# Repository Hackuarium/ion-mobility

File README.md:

# What is Ion Mobility Spectrometry ?

[https://en.wikipedia.org/wiki/Ion-mobility_spectrometry]

# Why should we do this ?

There are numerous application for IMS and it has the main advantage to work at atmospheric pressure (in constraste with mass spectrometry that requires most of the time 10-3 torr) that would make it compact and affordable.

We see the possibility to make continious monitoring of the bioreactor made by Hackuarium and situated in Cali, Colombia.

# Can we do a Ion Mobility Spectrometer our self ?

Main parts of the IMS :

- Desolvation zone : Insert and ionization of sample. 
Electrospray ionisation (ESI). Advantage : one can insert the liquid sample and ionize it through the same needle. 
Limitation : 5kV voltage source, 100uL/min flow rate through the needle. 

- Shutter : Let the ions pass on command.
Three grid Shutter. Advantage : easy to built and to command. 

- Drift zone : Acceleration of ions.
Made by multiple electrodes connected to different voltages with the aid of a voltage divider. 
Limitation : 10kV voltage source. 

- Detection : Faraday plate.
Transconductance amplifier converts the tiny ion current into a reasonable tension.
Limitation : The current-to-tension AOP must be with very low bias current, and low noise (hence expensive). 

- Monitoring : A/D converter. 

Link to full project already made : [https://github.com/bhclowers/OS-IMS]

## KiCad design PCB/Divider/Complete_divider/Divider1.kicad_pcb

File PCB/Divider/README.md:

# Divider

## Description

Printed circuit board of the two voltage dividers for the desolvation region and the drift tube/region. Connects all electrodes together with 10 M $\Omega$ in between each of them, to create a continuous voltage gradient and thus an electric field to accelerate the ions. 

## Specifications and limitations

The highest voltage is 11.5 kV at the first electrode, down to the ground connected last electrode, and the target at the end of the drift tube.

Higher resistors in between the electrodes doesn't change the voltage gradient but reduces the current and thus the electrical consumption.

## PCB

Below are pictures of the PCBs. First one is desolvation region and second one is drift region.

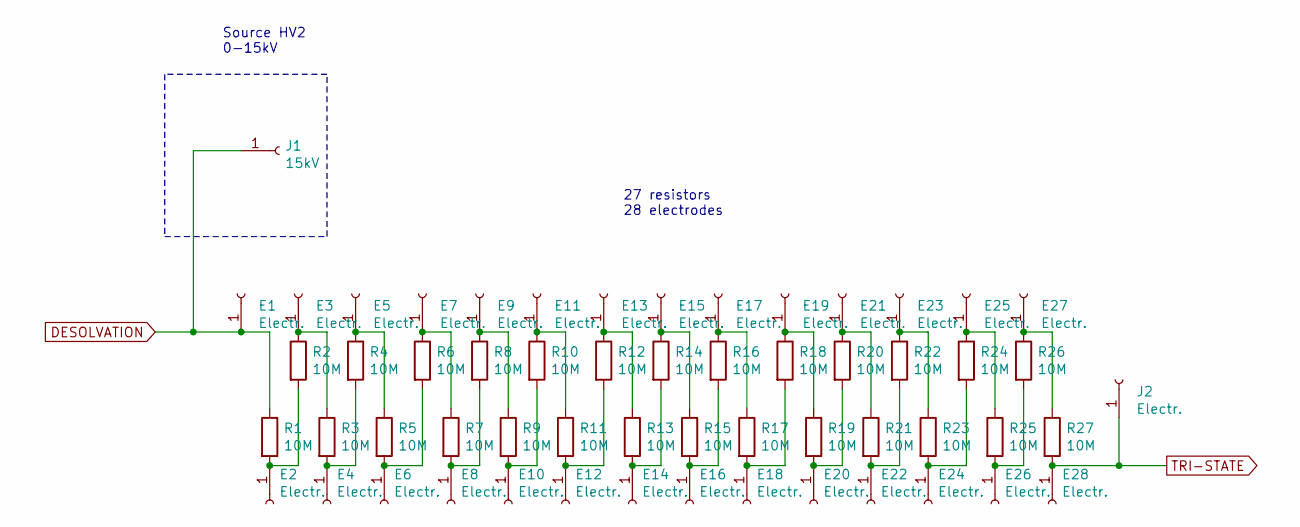
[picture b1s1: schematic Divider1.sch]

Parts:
E1, E2, E3, E4, E5, E6, E7, E8, E9, E10, E11, E12, E13, E14, E15, E16, E17, E18, E19, E20, E21, E22, E23, E24, E25, E26, E27, E28: Electr.; Pad_for_electrode
J1: 15kV; Pin_D1.4mm_L8.5mm_W2.8mm_FlatFork
J2: Electr.; Pin_D1.0mm_L10.0mm
R1, R2, R3, R4, R5, R6, R7, R8, R9, R10, R11, R12, R13, R14, R15, R16, R17, R18, R19, R20, R21, R22, R23, R24, R25, R26, R27: 10M; R_1206_3216Metric_Pad1.42x1.75mm_HandSolder

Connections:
DESOLVATION: E1.1, J1.1, R1.1
unnamed: E2.1, R1.2, R2.2
unnamed: E3.1, R2.1, R3.1
unnamed: E4.1, R3.2, R4.2
unnamed: E5.1, R4.1, R5.1
unnamed: E6.1, R5.2, R6.2
unnamed: E7.1, R6.1, R7.1
unnamed: E8.1, R7.2, R8.2
unnamed: E9.1, R8.1, R9.1
unnamed: E10.1, R9.2, R10.2
unnamed: E11.1, R10.1, R11.1
unnamed: E12.1, R11.2, R12.2
unnamed: E13.1, R12.1, R13.1
unnamed: E14.1, R13.2, R14.2
unnamed: E15.1, R14.1, R15.1
unnamed: E16.1, R15.2, R16.2
unnamed: E17.1, R16.1, R17.1
unnamed: E18.1, R17.2, R18.2
unnamed: E19.1, R18.1, R19.1
unnamed: E20.1, R19.2, R20.2
unnamed: E21.1, R20.1, R21.1
unnamed: E22.1, R21.2, R22.2
unnamed: E23.1, R22.1, R23.1
unnamed: E24.1, R23.2, R24.2
unnamed: E25.1, R24.1, R25.1
unnamed: E26.1, R25.2, R26.2
unnamed: E27.1, R26.1, R27.1
TRI-STATE: E28.1, J2.1, R27.2

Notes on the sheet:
Source HV2 0-15kV
27 resistors 28 electrodes

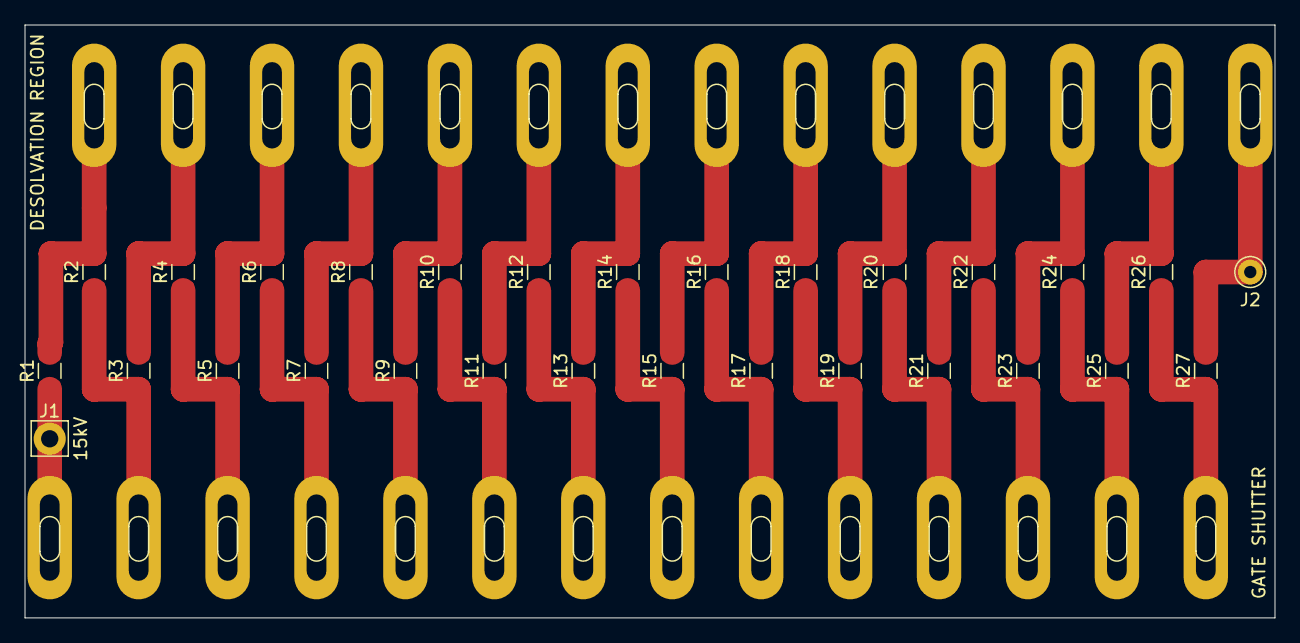
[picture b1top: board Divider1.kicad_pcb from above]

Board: 2 copper layers, 101.2 x 48.0 mm, 57 parts (0 on the bottom side), 28 nets.

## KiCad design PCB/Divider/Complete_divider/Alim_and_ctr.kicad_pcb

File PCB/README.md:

In order to better understand the overall electrical diagram and the paper’s resistance choice, an equivalent electrical diagram of the IMS from the first electrode to the amplifier is shown below. 

Thanks to those equations, we see that when the gate is closed, the potential of the second grid is higher than when it is opened. In the paper, they recommend adding 30 to 80 V (referenced to ”small” in the equations) to stop the flow of electrons. According to the calculations, a value of 50V or higher would result in a reverse electric field and effectively close the gate. 

These calculations are based on the paper’s values, not those of the current prototype. For the moment, the resistors on the divider PCB are 10 MΩ, designed to reduce power consumption. But this does not seem necessary, since with 1 MΩ resistors, power consumption is already only 160 to 200 μA, and changing the resistor of the dividers would also mean adapting the other resistors of the circuit.

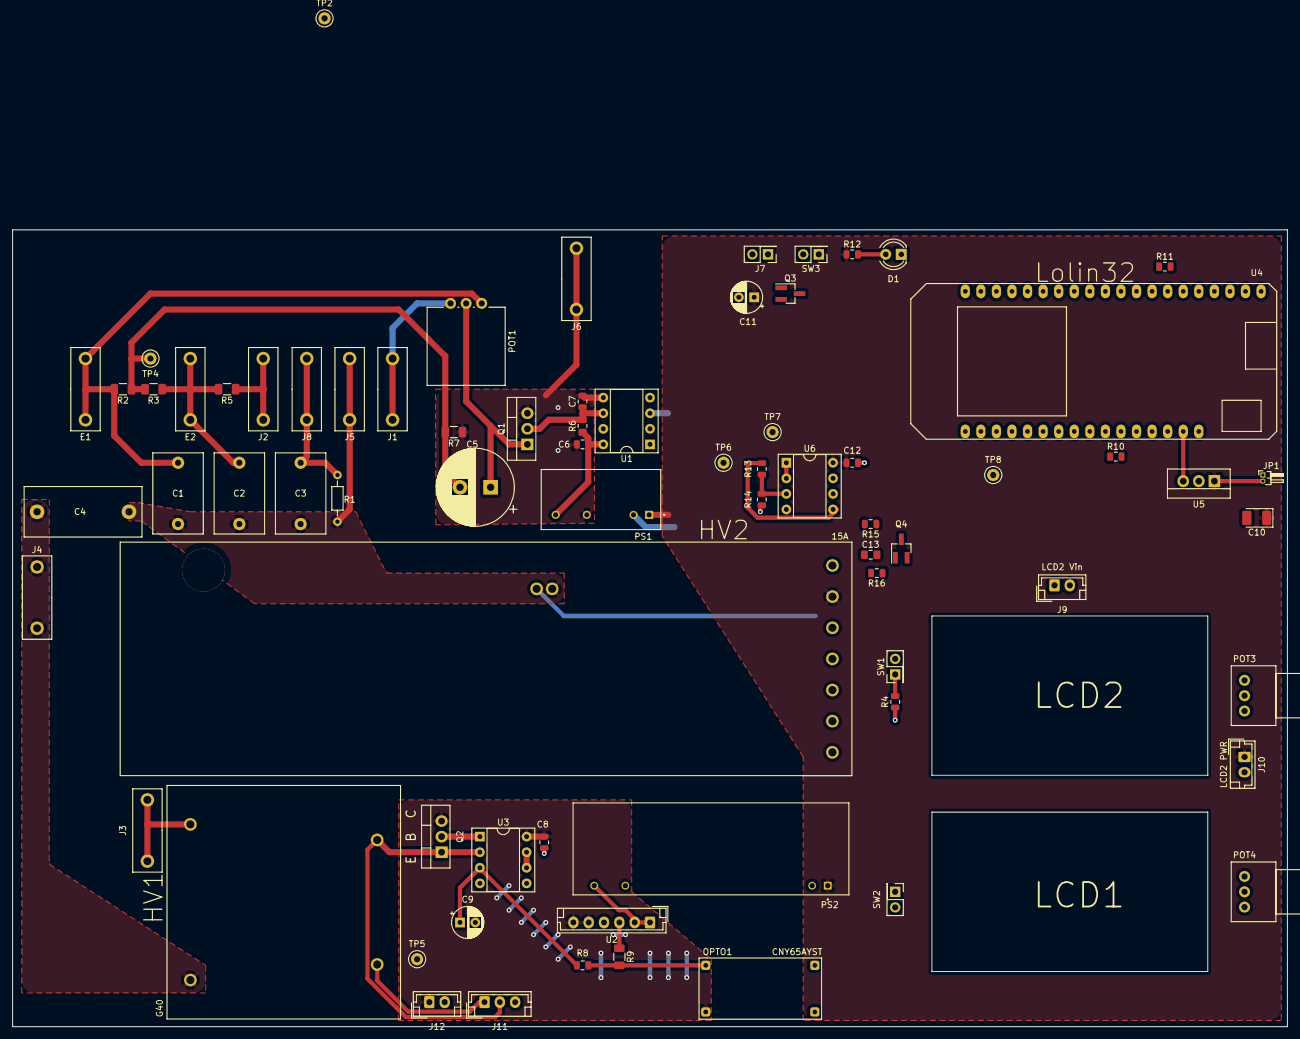
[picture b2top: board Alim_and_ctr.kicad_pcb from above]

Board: 2 copper layers, 208.0 x 130.0 mm, 72 parts (0 on the bottom side), 47 nets.

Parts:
C1, C2: 4700pF 10kV; C_Rect_L13.0mm_W8.0mm_P10.00mm_FKS3_FKP3_MKS4
C3: 0.22uF; C_Rect_L13.0mm_W8.0mm_P10.00mm_FKS3_FKP3_MKS4
C4: 2500pF 15 kV; C_Rect_L19.0mm_W8.0mm_P15.00mm_MKS4
C5: 47uF/100V; CP_Radial_D12.5mm_P5.00mm
C6, C8, C12: 100nF; C_0805_2012Metric
C7: 15pF; C_0805_2012Metric
C9: 2,2uF; CP_Radial_D5.0mm_P2.50mm
C10: 0.33uF Tant.; CP_EIA-3528-21_Kemet-B_Pad1.50x2.35mm_HandSolder
C11: 100uF; CP_Radial_D5.0mm_P2.50mm
C13: 2,2uF; C_0805_2012Metric_Pad1.15x1.40mm_HandSolder
D1: PWR LED; LED_D4.0mm
E1: Mid electrode1; conn_HV_JACK_PB1021
E2: Mid electrode2; conn_HV_JACK_PB1021
HV1: G40
HV2: 15A
J1: Electrode in; conn_HV_JACK_PB1021
J2: Electrode out; conn_HV_JACK_PB1021
J3, J4: HV out; conn_HV_JACK_PB1021
J5: Last Electrode; conn_HV_JACK_PB1021
J6: Gate; conn_HV_JACK_PB1021
J7: 12V in; PinHeader_2x01_P2.54mm_Vertical
J8: Ap Grid; conn_HV_JACK_PB1021
J9: LCD2 Vin; JST_EH_B2B-EH-A_1x02_P2.50mm_Vertical
J10: LCD2 PWR; JST_EH_B2B-EH-A_1x02_P2.50mm_Vertical
J11: LCD1 V/I measures; JST_EH_B3B-EH-A_1x03_P2.50mm_Vertical
J12: LCD1 PWR; JST_EH_B2B-EH-A_1x02_P2.50mm_Vertical
JP1: Jumper; PinHeader_1x02_P1.00mm_Horizontal
OPTO1: CNY65AYST
POT1: 10M; Potentiometer_Vishay_148-149_Single_Vertical
POT3, POT4: 50K; Potentiometer_Alps_RK097_Single_Horizontal
PS1: RHV2-1212S/R20; R8
PS2: RHV2-1212S/R20; R20
Q1: ZVN2110A; TO-220-3_Vertical
Q2: ZTX1053A; TO-220-3_Vertical
Q3: SSM3J340R; SOT-23_Handsoldering
Q4: ZTX1053A; SOT-23_Handsoldering
R1: 500K; R_Axial_DIN0204_L3.6mm_D1.6mm_P7.62mm_Horizontal
R2, R3: 1.5M; R_1206_3216Metric
R4, R14: 1M; R_0805_2012Metric
R5: 10M; R_1206_3216Metric
R6: 5K; R_0805_2012Metric_Pad1.15x1.40mm_HandSolder
R7: 50R; R_1206_3216Metric
R8, R15, R16: 20K; R_0805_2012Metric
R9: 1K; R_1206_3216Metric
R10, R11: 100R; R_0805_2012Metric
R12: R_LED; R_0805_2012Metric
R13: 3.3M; R_0805_2012Metric
SW1: EN switch; PinHeader_2x01_P2.54mm_Vertical
SW2: HV1 Switch; PinHeader_2x01_P2.54mm_Vertical
SW3: PWR switch; PinHeader_2x01_P2.54mm_Vertical
TP2, TP4, TP5, TP6, TP7, TP8: TestPoint; TestPoint_Keystone_5000-5004_Miniature
U1: 6N137A; DIP-8_W7.62mm_Socket
U2: mEZD41501A-X; JST_EH_B6B-EH-A_1x06_P2.50mm_Vertical
U3: LM358; DIP-8_W7.62mm_Socket
U4: Lolin32
U5: MC78M15ACTG; TO-262-3_Vertical
U6: LM358P; DIP-8_W7.62mm_Socket

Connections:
+3V3: POT3.1, POT4.1, U4.1, U4.20
+5V: JP1.1, Q4.3, U5.3
+12V: C10.1, C11.1, C12.2, HV2.2, J10.1, PS1.1, PS2.1, R12.1, SW3.1, U5.1, U6.8
+12VA: C6.1, PS1.4, R6.1, U1.8
+15V: C8.1, J12.1, OPTO1.4, Q2.3, U2.5, U2.6, U3.8
/Aperture_Grid: C3.1, J8.1, R1.1
/Middle_electrode1: C1.1, E1.1, POT1.3, R2.2
/Middle_electrode2: C2.1, E2.1, R3.1, R5.2
ADC1: POT3.2, U4.6
ADC2: POT4.2, U4.7
ADJ_HV2: C13.1, HV2.6, R15.2
ADJ_HV2_PWM: Q4.2, U4.5
ALIMHV1+: HV1.1, J11.2, Q2.1, TP5.1, U3.2
ALIMHV1-: HV1.2, J11.1
COUNTER_ELECTRODE: C4.1, HV1.4, HV2.10, J4.1
DRIFT_TUBE: J2.1, R5.1
EOUT: HV2.9, R13.1, TP6.1, U6.5
EOUTPIN: TP8.1, U4.8, U6.1, U6.2
GATE_IN+: C5.1, POT1.2, Q1.1, TP2.1
GATE_IN-: C5.2, R2.1, R3.2, R7.2, TP4.1
GATE_OUT: C6.2, C7.2, J6.1, PS1.3, Q1.3, R7.1, U1.5
GND: C10.2, C11.2, C12.1, C13.2, D1.1, HV2.1, J7.2, J9.2, J10.2, OPTO1.2, POT3.3, POT4.3, PS1.2, PS2.2, Q3.2, R4.1, R14.2, R16.2, U1.3, U4.16, U4.17, U4.23, U4.24, U4.34, U5.2, U6.4, U6.6
GNDB: C8.2, C9.2, J11.3, J12.2, PS2.3, R9.1, U2.3, U2.4, U3.4, U3.5
GRID_CTRL: R10.1, U1.2
IOUT: HV2.3, U4.13
LAST_ELECTRODE: C1.2, C2.2, C3.2, C4.2, HV2.8, J5.1, R1.2
LCD2_MEASURE: J9.1, U6.7
NEEDLE: HV1.3, J3.1
unnamed: C7.1, Q1.2, R6.2, U1.6
unnamed: C9.1, R8.2, U3.3
unnamed: D1.2, R12.2
unnamed: HV2.4, SW1.2
unnamed: J7.1, Q3.1
unnamed: JP1.2, U4.15
unnamed: OPTO1.3, R8.1, R9.2
unnamed: PS2.4, U2.1, U2.2
unnamed: Q2.2, U3.1
unnamed: Q3.3, SW3.2
unnamed: Q4.1, R15.1, R16.1
unnamed: R4.2, SW1.1
unnamed: R10.2, U4.11
unnamed: R11.1, SW2.1
unnamed: R11.2, U4.30
unnamed: R13.2, R14.1, TP7.1, U6.3
unnamed: U3.6, U3.7
PWM: OPTO1.1, SW2.2
TRI-STATE: J1.1, POT1.1

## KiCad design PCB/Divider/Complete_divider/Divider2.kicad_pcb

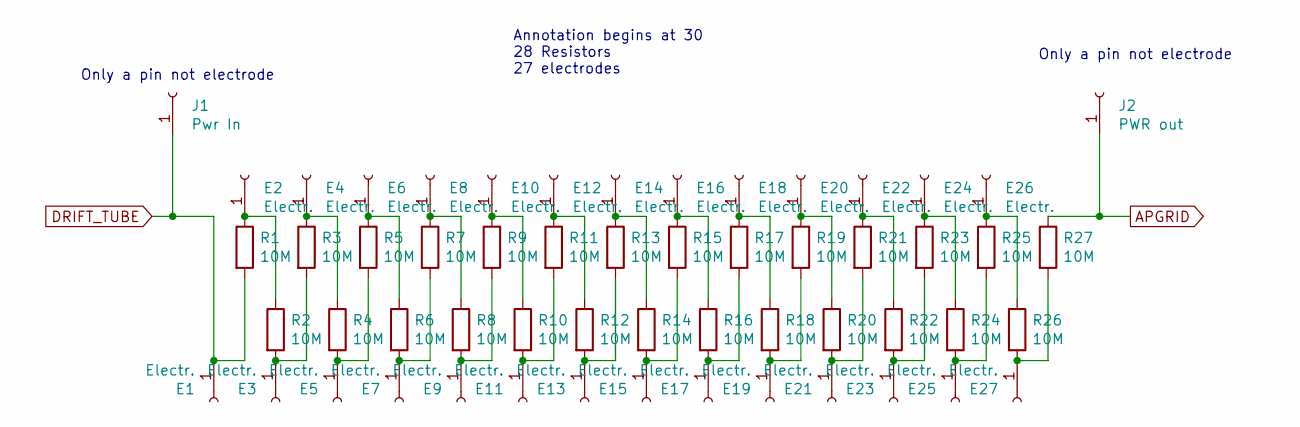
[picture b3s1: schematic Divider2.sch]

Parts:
E1, E2, E3, E4, E5, E6, E7, E8, E9, E10, E11, E12, E13, E14, E15, E16, E17, E18, E19, E20, E21, E22, E23, E24, E25, E26, E27: Electr.; Pad_for_electrode
J1: Pwr In; Pin_D1.0mm_L10.0mm
J2: PWR out; Pin_D1.0mm_L10.0mm
R1, R2, R3, R4, R5, R6, R7, R8, R9, R10, R11, R12, R13, R14, R15, R16, R17, R18, R19, R20, R21, R22, R23, R24, R25, R26, R27: 10M; R_1206_3216Metric

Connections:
APGRID: J2.1, R27.1
DRIFT_TUBE: E1.1, J1.1, R1.2
unnamed: E2.1, R1.1, R2.1
unnamed: E3.1, R2.2, R3.2
unnamed: E4.1, R3.1, R4.1
unnamed: E5.1, R4.2, R5.2
unnamed: E6.1, R5.1, R6.1
unnamed: E7.1, R6.2, R7.2
unnamed: E8.1, R7.1, R8.1
unnamed: E9.1, R8.2, R9.2
unnamed: E10.1, R9.1, R10.1
unnamed: E11.1, R10.2, R11.2
unnamed: E12.1, R11.1, R12.1
unnamed: E13.1, R12.2, R13.2
unnamed: E14.1, R13.1, R14.1
unnamed: E15.1, R14.2, R15.2
unnamed: E16.1, R15.1, R16.1
unnamed: E17.1, R16.2, R17.2
unnamed: E18.1, R17.1, R18.1
unnamed: E19.1, R18.2, R19.2
unnamed: E20.1, R19.1, R20.1
unnamed: E21.1, R20.2, R21.2
unnamed: E22.1, R21.1, R22.1
unnamed: E23.1, R22.2, R23.2
unnamed: E24.1, R23.1, R24.1
unnamed: E25.1, R24.2, R25.2
unnamed: E26.1, R25.1, R26.1
unnamed: E27.1, R26.2, R27.2

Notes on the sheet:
Annotation begins at 30 28 Resistors 27 electrodes
Only a pin not electrode

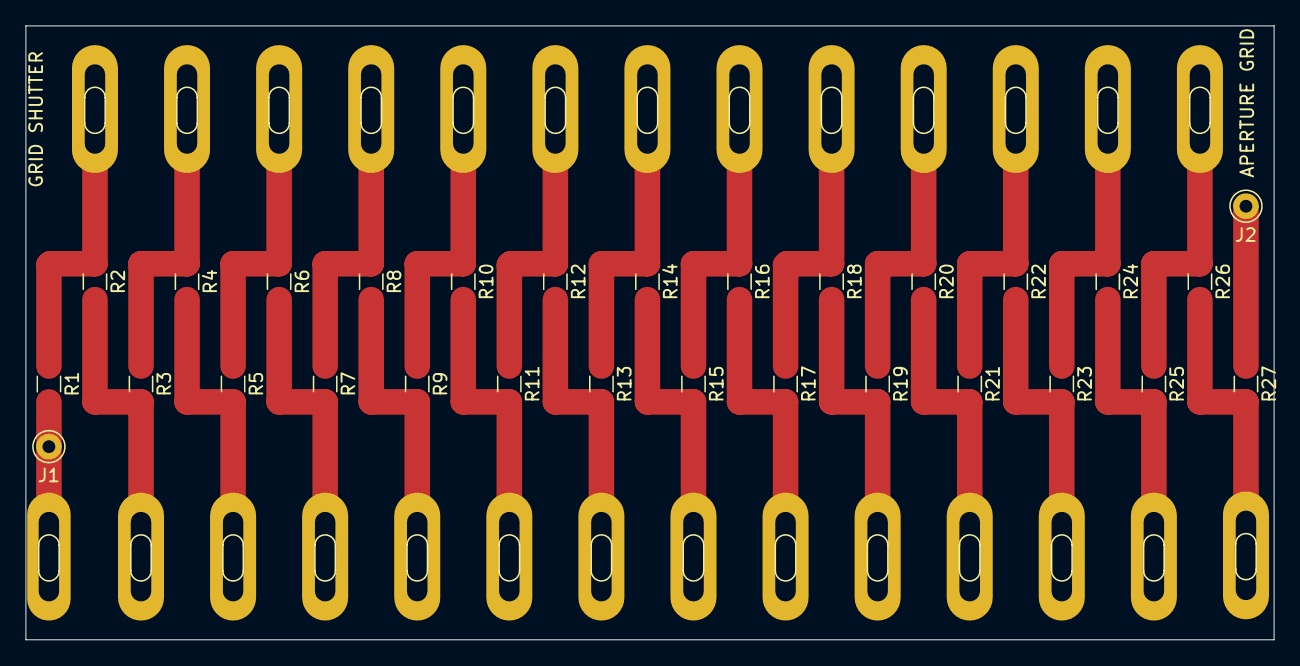
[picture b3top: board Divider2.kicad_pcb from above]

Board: 2 copper layers, 97.6 x 48.0 mm, 56 parts (0 on the bottom side), 28 nets.

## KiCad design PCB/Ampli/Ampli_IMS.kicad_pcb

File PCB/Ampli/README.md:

# Amplification stage

## Description

Amplification stage to transform the small current on the target to an acceptable voltage to be read/processed. 

[Transimpedance circuit](https://en.wikipedia.org/wiki/Transimpedance_amplifier) with a big gain (10^8) and a voltage follower through a dual precision operationnal amplifier (Texas Instruments LMC6082).

## Specifications and limitations

The circuit needs to be as close as possible to the target of the IMS in order to limit the noise present on the signal. One possibility is to solder the PCB directly on the back of the target. 

Possible amplification of the noise must be taken into account, and possibly filtered through a very small capacitor (~0.01 pF, thus quite expensive) in the gain stage feedback loop (a bigger resistor amplifies the signal but also the noise).

## PCB

Below is a picture of the mounted PCB, currently missing the connectors and a potential filtering capacitor C1.

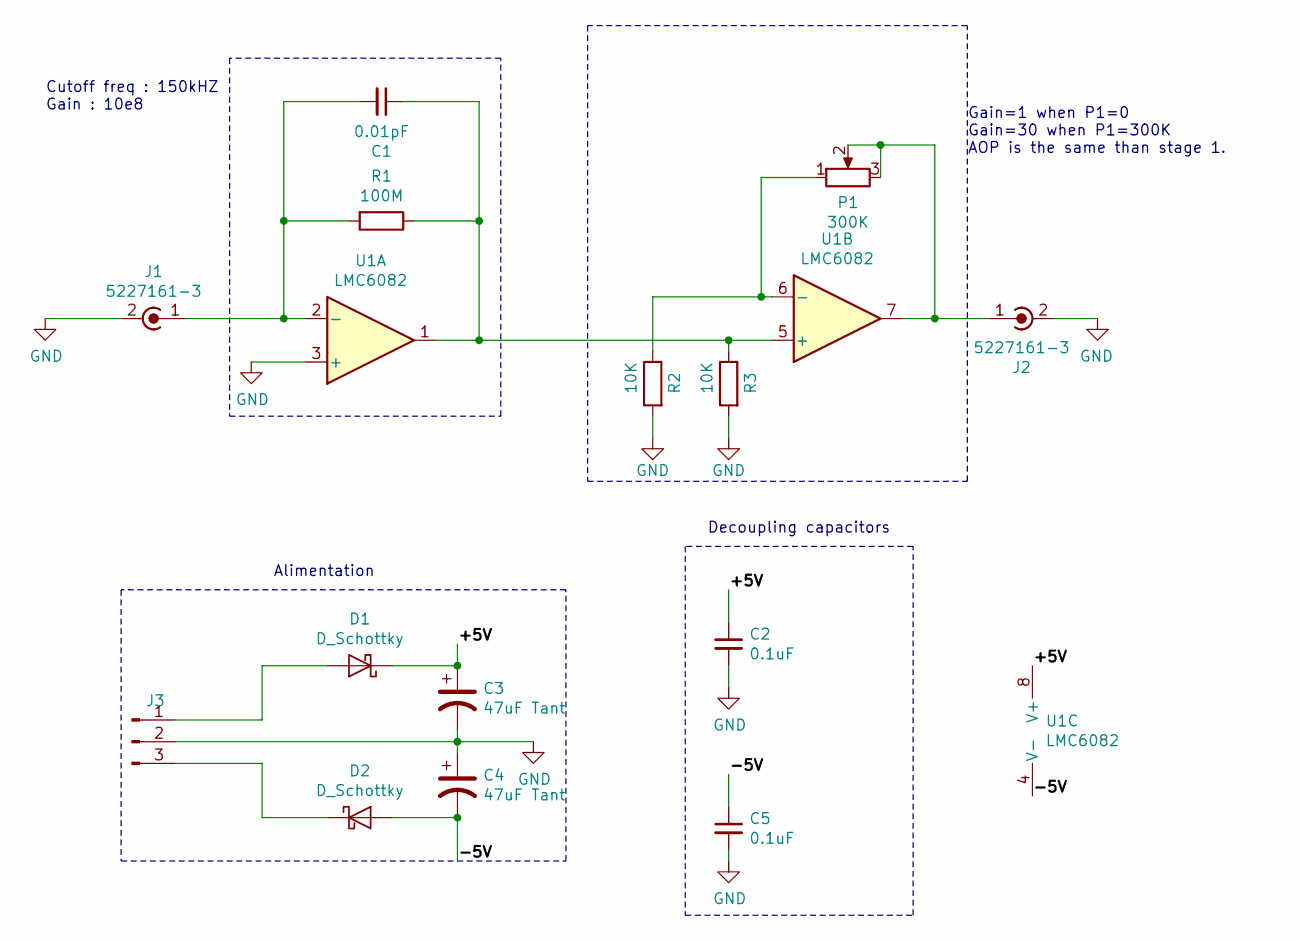
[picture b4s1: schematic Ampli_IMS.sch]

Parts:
C1: 0.01pF; C_0805_2012Metric
C2, C5: 0.1uF; C_0805_2012Metric
C3, C4: 47uF Tant; CP_EIA-3216-18_Kemet-A_Pad1.58x1.35mm_HandSolder
D1, D2: D_Schottky; D_0805_2012Metric_Castellated
J1: 5227161-3; SMA_Amphenol_132203-12_Horizontal
J2: 5227161-3; BNC_Amphenol_B6252HB-NPP3G-50_Horizontal
J3: Conn_01x03_Male; JST_EH_B3B-EH-A_1x03_P2.50mm_Vertical
P1: 300K; Potentiometer_Alps_RK09Y11_Single_Horizontal
R1: 100M; C_0805_2012Metric
R2, R3: 10K; C_0805_2012Metric
U1: LMC6082; SO-8_3.9x4.9mm_P1.27mm

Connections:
/+5V: C2.1, C3.1, D1.1 (K), U1.8 (V+)
/-5V: C4.2, C5.1, D2.2 (A), U1.4 (V-)
GND: C2.2, C3.2, C4.1, C5.2, J1.2 (Ext), J2.2 (Ext), J3.2, R2.2, R3.2, U1.3 (+)
unnamed: C1.1, R1.1, R3.1, U1.1, U1.5 (+)
unnamed: C1.2, J1.1 (In), R1.2, U1.2 (-)
unnamed: D1.2 (A), J3.1
unnamed: D2.1 (K), J3.3
unnamed: J2.1 (In), P1.2, P1.3, U1.7
unnamed: P1.1, R2.1, U1.6 (-)

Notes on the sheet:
Decoupling capacitors
Alimentation
Gain=1 when P1=0 Gain=30 when P1=300K AOP is the same than stage 1.
Cutoff freq : 150kHZ Gain : 10e8

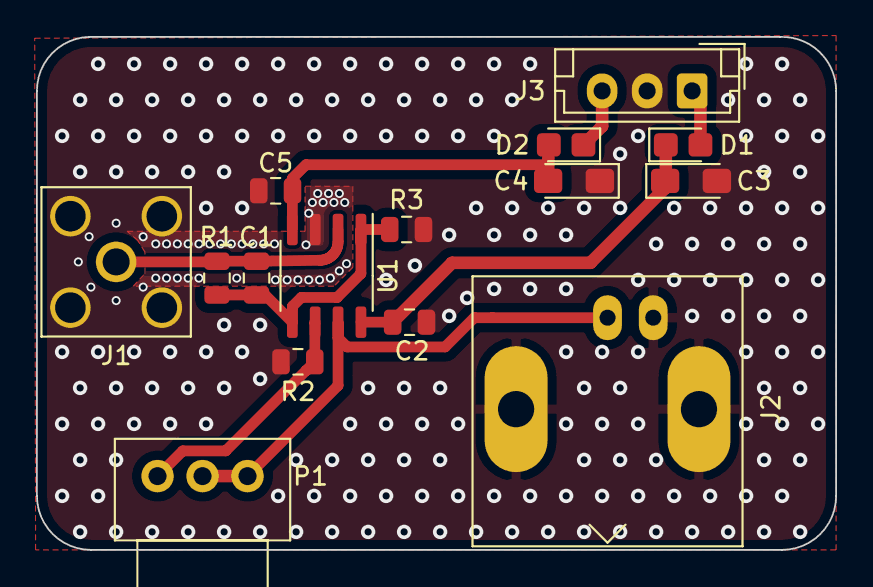
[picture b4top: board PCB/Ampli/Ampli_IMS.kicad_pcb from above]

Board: 2 copper layers, 44.4 x 28.5 mm, 15 parts (0 on the bottom side), 9 nets.

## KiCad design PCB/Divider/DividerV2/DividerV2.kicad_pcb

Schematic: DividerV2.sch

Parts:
C1, C2, C3: 4700pF 10kV; C_Rect_L13.0mm_W8.0mm_P10.00mm_FKS3_FKP3_MKS4
E1, E2, E3, E4, E5, E6, E7, E8, E9, E10, E11, E12, E13, E14, E15, E16, E17, E18, E19, E20, E21, E22, E23, E24, E25, E26, E27, E28, E29: Electr.; Pad_for_electrode
J1: 15kV; Pin_D1.4mm_L8.5mm_W2.8mm_FlatFork
J2, J4: 10kV; Pin_D1.4mm_L8.5mm_W2.8mm_FlatFork
J3: 0V; Pin_D1.4mm_L8.5mm_W2.8mm_FlatFork
R1, R2, R3, R4, R5, R6, R7, R8, R9, R10, R11, R12, R13, R14, R15, R16, R17, R18, R19, R20, R21, R22, R23, R24, R25, R26, R27, R28, R29: 10M; R_1206_3216Metric_Pad1.42x1.75mm_HandSolder
R30: 500K; R_Axial_DIN0207_L6.3mm_D2.5mm_P15.24mm_Horizontal
R31, R33: 1.5M; R_1206_3216Metric
R32: 100M; R_1206_3216Metric
R34, R35, R36, R37, R38, R39, R40, R41, R42, R43, R44, R45, R46, R47, R48, R49, R50, R51, R52, R53, R54, R55, R56, R57, R58, R59, R60, R61, R62: 10M; R_1206_3216Metric
RV1: 100M; Potentiometer_ACP_CA14-H4_Horizontal
U1: SFH617A-1; DIP-4_W7.62mm

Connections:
/ApertureGrid: C3.1, R30.1
/Drift_tube: E1.1, J2.1, J4.1, R15.1
/ESI: J1.1
/Grid1: C1.1, R31.1, RV1.3
/Grid2: R32.2, U1.3
APGRID: R48.1
DRIFTTUBE: C2.1, R33.2, R34.2
GND: C1.2, C2.2, C3.2, J3.1, R30.2, U1.2
unnamed: E2.1, R1.1, R16.1
unnamed: E3.1, R2.1, R17.1
unnamed: E4.1, R3.1, R18.1
unnamed: E5.1, R4.1, R19.1
unnamed: E6.1, R5.1, R20.1
unnamed: E7.1, R6.1, R21.1
unnamed: E8.1, R7.1, R22.1
unnamed: E9.1, R8.1, R23.1
unnamed: E10.1, R9.1, R24.1
unnamed: E11.1, R10.1, R25.1
unnamed: E12.1, R11.1, R26.1
unnamed: E13.1, R12.1, R27.1
unnamed: E14.1, R13.1, R28.1
unnamed: E15.1, R14.1, R29.1
unnamed: E16.1, R1.2, R15.2
unnamed: E17.1, R2.2, R16.2
unnamed: E18.1, R3.2, R17.2
unnamed: E19.1, R4.2, R18.2
unnamed: E20.1, R5.2, R19.2
unnamed: E21.1, R6.2, R20.2
unnamed: E22.1, R7.2, R21.2
unnamed: E23.1, R8.2, R22.2
unnamed: E24.1, R9.2, R23.2
unnamed: E25.1, R10.2, R24.2
unnamed: E26.1, R11.2, R25.2
unnamed: E27.1, R12.2, R26.2
unnamed: E28.1, R13.2, R27.2
unnamed: E29.1, R14.2, R28.2
unnamed: R31.2, R32.1, R33.1
unnamed: R34.1, R49.1
unnamed: R35.1, R50.1
unnamed: R35.2, R49.2
unnamed: R36.1, R51.1
unnamed: R36.2, R50.2
unnamed: R37.1, R52.1
unnamed: R37.2, R51.2
unnamed: R38.1, R53.1
unnamed: R38.2, R52.2
unnamed: R39.1, R54.1
unnamed: R39.2, R53.2
unnamed: R40.1, R55.1
unnamed: R40.2, R54.2
unnamed: R41.1, R56.1
unnamed: R41.2, R55.2
unnamed: R42.1, R57.1
unnamed: R42.2, R56.2
unnamed: R43.1, R58.1
unnamed: R43.2, R57.2
unnamed: R44.1, R59.1
unnamed: R44.2, R58.2
unnamed: R45.1, R60.1
unnamed: R45.2, R59.2
unnamed: R46.1, R61.1
unnamed: R46.2, R60.2
unnamed: R47.1, R62.1
unnamed: R47.2, R61.2
unnamed: R48.2, R62.2
unnamed: RV1.2, U1.4
TRI-STATE: R29.2, RV1.1

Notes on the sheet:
5kV
INFO : 10M par résistance, soit un courant total de 10kV/580M = 0.001724A = 17.24uA
Source #2 0-10kV
Source #1 0-5kV

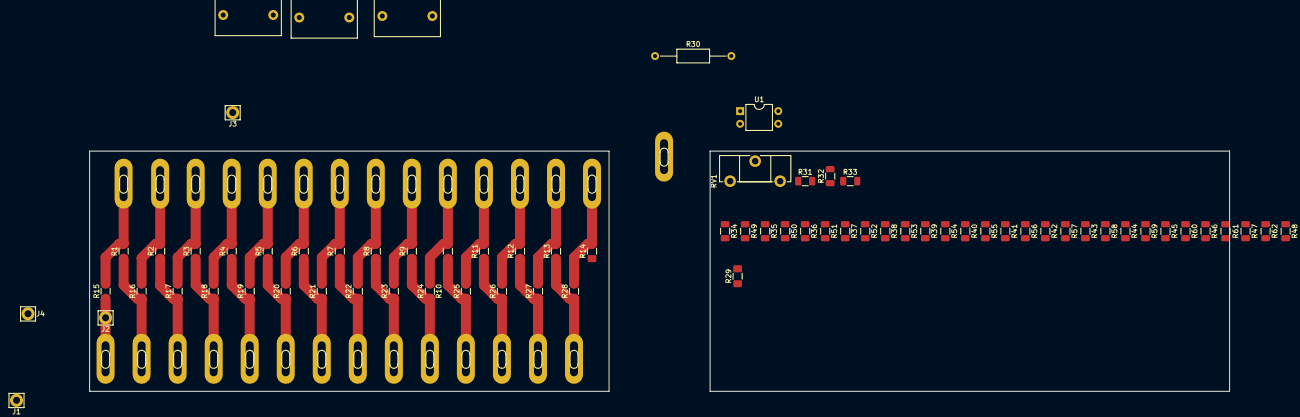
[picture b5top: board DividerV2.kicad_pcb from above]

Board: 2 copper layers, 227.8 x 48.0 mm, 100 parts (0 on the bottom side), 65 nets.

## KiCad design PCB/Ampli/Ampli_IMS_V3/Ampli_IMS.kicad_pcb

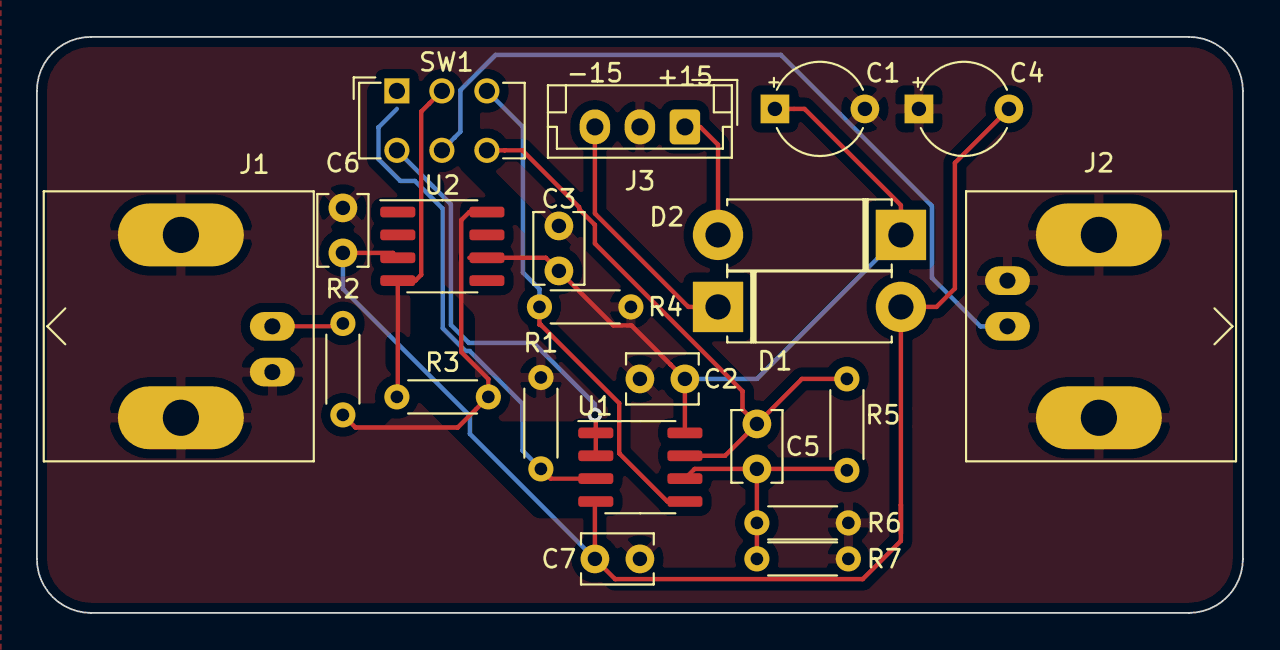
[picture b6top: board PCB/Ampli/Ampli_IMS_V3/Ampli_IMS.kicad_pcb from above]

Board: 2 copper layers, 67.0 x 32.0 mm, 22 parts (0 on the bottom side), 14 nets.

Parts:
C1, C4: 47uF Tant; CP_Radial_Tantal_D5.0mm_P5.00mm
C2, C3, C6, C7: 0.1uF; C_Disc_D3.8mm_W2.6mm_P2.50mm
C5: C_Small; C_Disc_D3.8mm_W2.6mm_P2.50mm
D1, D2: D_Schottky; D_5W_P10.16mm_Horizontal
J1, J2: 5227161-3; BNC_Amphenol_B6252HB-NPP3G-50_Horizontal
J3: Conn_01x03_Male; JST_EH_B3B-EH-A_1x03_P2.50mm_Vertical
R1, R2, R4: 10K MF 1/4W; R_Axial_DIN0204_L3.6mm_D1.6mm_P5.08mm_Horizontal
R3: 100M 1/4W; R_Axial_DIN0204_L3.6mm_D1.6mm_P5.08mm_Horizontal
R5: 9.09K MF 0.6W; R_Axial_DIN0204_L3.6mm_D1.6mm_P5.08mm_Horizontal
R6: 1.13K MF 1/4W; R_Axial_DIN0204_L3.6mm_D1.6mm_P5.08mm_Horizontal
R7: 6.65K MF 1/2W; R_Axial_DIN0204_L3.6mm_D1.6mm_P5.08mm_Horizontal
SW1: SS22D0205G2; SW_CuK_JS202011CQN_DPDT_Straight
U1: LT1464CS8; SOIC-8_3.9x4.9mm_P1.27mm
U2: LMP7721; SOIC-8_3.9x4.9mm_P1.27mm

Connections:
/+15V: C1.1, C2.1, C3.1, D1.1, U1.8, U2.6
/-15V: C4.2, C6.1, C7.1, D2.2, U1.4, U2.3
GND: C1.2, C2.2, C3.2, C4.1, C6.2, C7.2, J1.2, J2.2, J3.2, R1.2, R4.2, R6.2, R7.2
unnamed: C5.1, R5.1, SW1.6, U1.7
unnamed: C5.2, R5.2, R6.1, R7.1, U1.6
unnamed: D1.2, J3.1
unnamed: D2.1, J3.3
unnamed: J1.1, R2.2
unnamed: J2.1, SW1.5
unnamed: R1.1, SW1.1, U1.3
unnamed: R2.1, R3.2, U2.8
unnamed: R3.1, SW1.2, U2.4
unnamed: R4.1, SW1.3, U1.5
unnamed: SW1.4, U1.1, U1.2

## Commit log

2019-10-05 Rename Shutter_info.txt to Shutter_info.md
2019-10-06 Create Ionization_info
2019-10-06 Rename Ionization_info to Ionization_info.md
2019-10-06 Add files via upload
    Electrospray
2019-10-16 Create Additionnal stuff
2019-11-30 add pcb from publication
2019-12-01 add gitignore
2019-12-01 chore: update boards on pcbway requests
2020-03-05 test_changement_de_nom
2020-03-05 ajout du catia
2020-03-05 refactorm
2020-03-05 test_change
2020-03-05 fin_test
2020-03-05 PCB for voltage divider
2020-03-05 reorganisation
2020-03-05 modif of schematics
2020-03-06 Change name
2020-03-06 Moved parts
2020-03-06 tracks realised
2020-03-06 Dimensions of pcb
    Power parts brought together, and length of pcb smaller
2020-03-06 Power tracks enlarged
2020-03-06 Signal tracks enlarged
2020-03-06 Footprint changes
2020-03-06 Begin PCB of divider
2020-03-06 divider
2020-03-07 Pbs with footprints
2020-03-07 PCB + new electrodes
2020-03-07 1st pcb done
2020-03-07 added tips about low noise pcb design
2020-03-08 catia update
2020-03-08 Divider1: Without tracks
2020-03-08 Reorganize
2020-03-08 Dividers finished without testing points
2020-03-08 Divider finished with test points
2020-03-08 Most parts completed
2020-03-09 low noise pcb design
2020-03-10 Small corrections
2020-03-10 Revert "Small corrections"
2020-03-10 Low noise smd amp
2020-03-10 SMD + low noise design
2020-03-11 low noise features
2020-03-11 Small mistakes
2020-03-11 pcd target added
2020-03-21 GND guards are neat!
2020-03-22 Implementation of the HV sources footprints and schems
2020-03-24 Small modifications
2020-03-25 Implementing MCU
2020-03-25 Labelling/ordering stuff
2020-04-07 Small modif
2020-04-08 DC/DC isolated converter implementation
2020-04-09 Set a Vin of 5V
2020-04-09 Small changes
2020-04-09 Implementation of ESP32 code
2020-04-09 New version of code
2020-04-11 Simplification of the functions
2020-04-17 New isolated alimentation design
2020-04-29 Modifications of the amplification part
2020-06-01 Voltage measure circuits
2020-06-02 Begin PCB design
2020-06-02 Components in place
2020-06-05 Electrode design
2020-06-05 HV design finished
2020-06-08 Improve PCBs
2020-06-08 code update: final file is in test4
2020-06-11 Ampli last version - low noise guarding
2020-06-11 Alim&control update
2020-06-12 Updates of dividers 1 & 2
2020-07-13 Complete divider update
2023-06-01 Create README for ampli
2023-06-01 Add README files
2023-06-01 Add new CAD files version V2
    New CAD files for version V2 of 3D printed IMS. New folders created to reorganize CAD files in efficient way.
2023-06-02 Update README.md
    Bug correction
2023-06-02 Update README.md
    readme CAD V2
2023-06-03 Nafion specification
2023-06-05 add pictures in README.md
2023-06-05 Update README.md ampli
2023-06-08 Add V3 IMS CAD version
2023-06-09 README update
2023-06-09 Ajout readme
